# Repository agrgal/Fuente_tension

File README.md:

# Fuente_tension
 Esquemas y diseño de la fuente de tensión con DSP-5015-USB

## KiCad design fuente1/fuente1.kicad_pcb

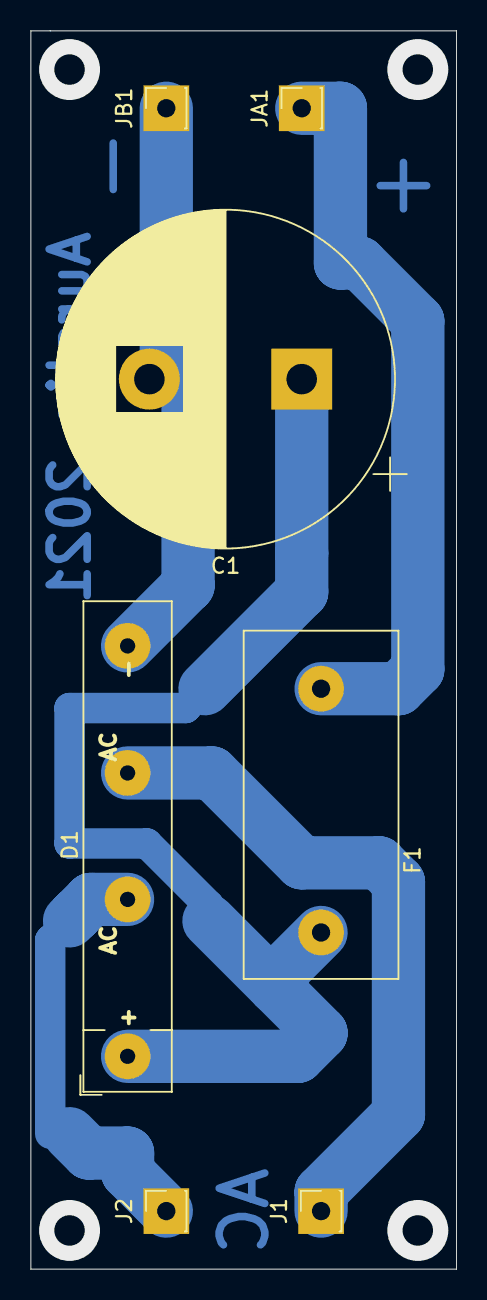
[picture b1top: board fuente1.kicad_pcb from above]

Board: 2 copper layers, 27.9 x 81.3 mm, 7 parts (0 on the bottom side), 5 nets.

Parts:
C1: 4700uF 50V; CP_Radial_D22.0mm_P10.00mm_SnapIn
D1: Puente_Diodos; Diode_Bridge_FAGOR
F1: Fuse; Fusible_Personalizado
J1, J2: Screw_Terminal_01x01; PinSocket_1x01_P2.54mm_Vertical
JA1: Screw_Terminal_01x01; PinSocket_1x01_P2.54mm_Vertical
JB1: Screw_Terminal_01x01; PinSocket_1x01_P2.54mm_Vertical

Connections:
unnamed: C1.1, D1.1, F1.2
unnamed: C1.2, D1.2, JB1.1
unnamed: D1.3, J1.1
unnamed: D1.4, J2.1
unnamed: F1.1, JA1.1

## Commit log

2022-08-29 Inclusión de fuente definitiva
    Con estos ficheros actualizo el resultado final
2022-12-10 Create Conseguido.txt
    dgffgdf
